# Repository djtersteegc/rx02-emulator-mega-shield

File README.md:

# rx02-emulator-mega-shield

Arduino Mega2560 shield with buttons and LCD based on [AK6DN's DEC RX02 emulator](https://github.com/AK6DN/rx02_emulator) board design and code.  There is a fork of his project at  https://github.com/djtersteegc/rx02_emulator that adds software support for the new board design.

You can also still run it via the original serial terminal command scheme.  If you don't want to build it with the LCD or buttons, you can disable supprort in the code by leaving

`#define USE_LCD_MENU`

commented out (undefined) in `my_project.h`

Resistor numbers is also different than AK6DN's original board so please refer to this mapping table below or the CSV file.

[Termination Resistor Table.csv](https://github.com/djtersteegc/rx02-emulator-mega-shield/blob/main/Termination%20Resistor%20Table.csv)

Most of the resistor footprints should NOT be populated.

| Signal         | Resistor | Value   | Resistor | Value   |
| -------------- | -------- | ------- | -------- | ------- |
| RX_DMA_MODE_H  | R2       | -       | R1       | **390** |
| RX_AC_L        | R4       | **120** | R3       | -       |
| RX_OUT_L       | R6       | -       | R5       | -       |
| RX_SHIFT_L     | R8       | -       | R7       | -       |
| RX_12BIT_L     | R10      | **180** | R9       | **390** |
| RX_DATA_L      | R12      | **180** | R11      | **390** |
| RX_DONE_L      | R14      | -       | R13      | -       |
| RX_XFER_RQST_L | R16      | -       | R15      | -       |
| RX_INIT_L      | R18      | -       | R17      | **390** |
| RX_ERROR_L     | R20      | -       | R19      | -       |
| RX_RUN_L       | R23      | **180** | R22      | **390** |

STL's and the [DesignSpark Mechanical](https://www.rs-online.com/designspark/mechanical-software) source file for an snap fit enclosure are in the **enclosure** directory. There is also a provision to secure it with one M3x6mm (or longer) screw if you want.  Since the power and USB port spacing on the Chinese clone Arduino Mega2560's with the CH340 serial chip is different than the original design there are two STL's for the case body, pick the one that matches your board.

All components can be sourced from the usual low cost China based vendors for a total build cost of around $20.  Please see the assembly page for more details.

[Hardware Component Choices and Assembly](https://djtersteegc.github.io/rx02-emulator-mega-shield/assembly.html)

An interactive BOM and parts placement diagram is also available.

[Interactive Bill of Materials (BOM)](https://djtersteegc.github.io/rx02-emulator-mega-shield/ibom.html)

# Getting a Board

You can download the Gerbers and use your favorite fab (JLCPCB, PCBWay, etc.) to make your own batch.  It's a standard two layer, 1oz copper board with dimensions of 99mm x 71mm so it squeaks under the 100mm x 100mm limit of the cheap Chinese fabs.

# Hardware Revisions

### Version 1.0

After designing and building the [Mega Pro SMD](https://github.com/djtersteegc/rx02-mega2560-pro) version of this, I discovered the reason you always had to do a ReINIT of the emulator to get it recognized was I failed to pick interrupt enabled pins on the Mega2560 for the RX_INIT and RX_RUN lines.  This has been corrected in the v1.1 board and you can fix this yourself in v1.0 by adding two jumper  wires from D22 to D2, and D26 to D3.  Once complete, reflash with the updated version of the code at https://github.com/djtersteegc/rx02_emulator 

### Version 1.1

Moved the RX_INIT and RX_RUN lines to interrupt enabled pins on the Mega2560.

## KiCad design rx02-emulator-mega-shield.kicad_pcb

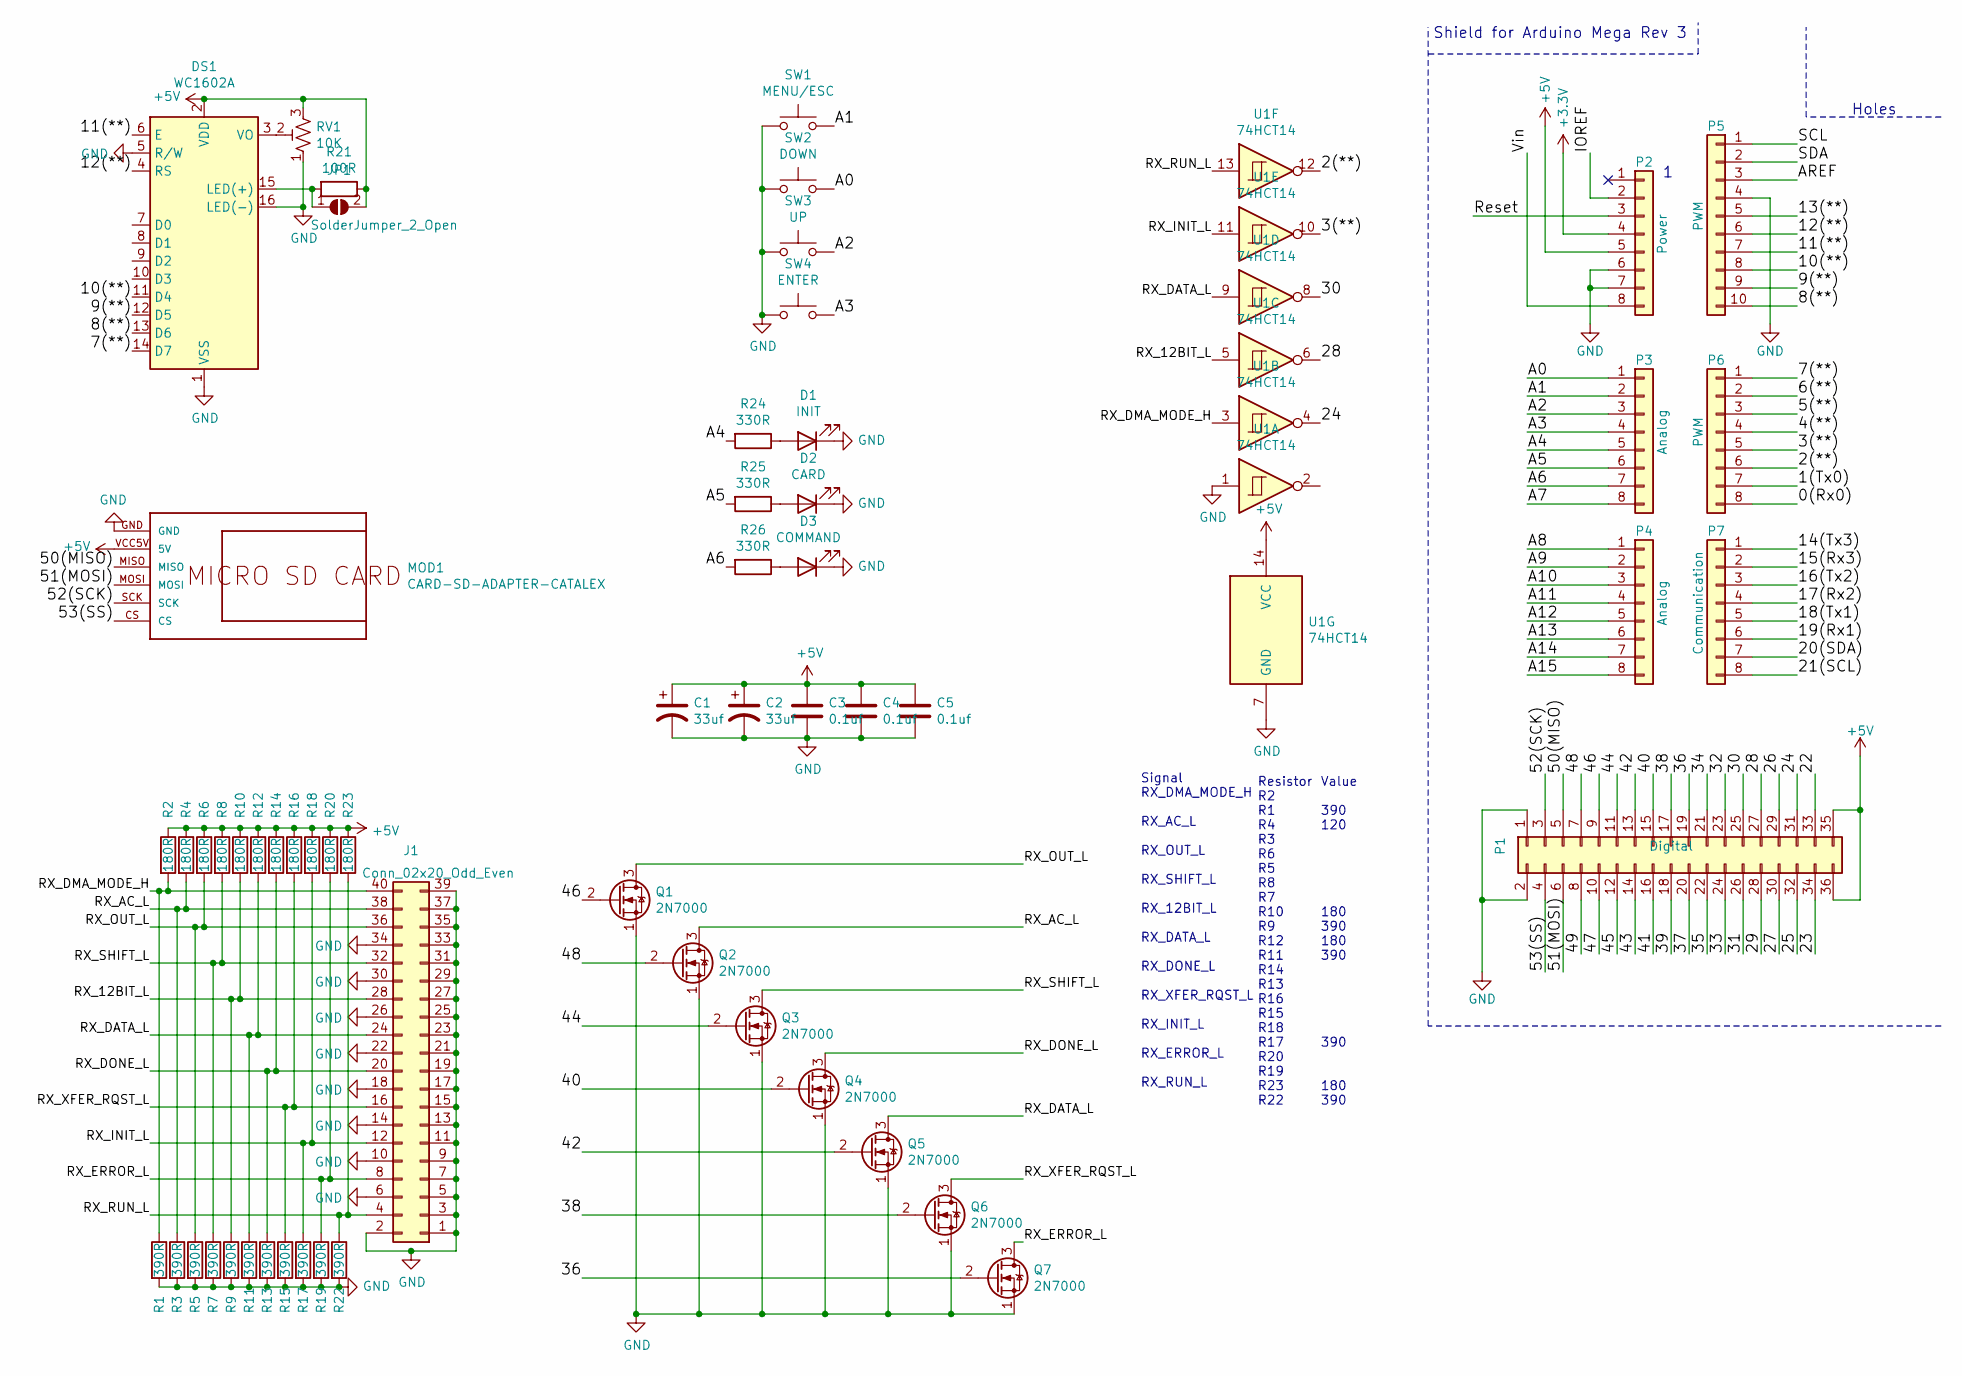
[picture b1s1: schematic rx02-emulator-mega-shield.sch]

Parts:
C1, C2: 33uf; CP_Radial_D5.0mm_P2.50mm
C3, C4, C5: 0.1uf; C_Disc_D5.0mm_W2.5mm_P5.00mm
D1: INIT; LED_D5.0mm
D2: CARD; LED_D5.0mm
D3: COMMAND; LED_D5.0mm
DS1: WC1602A
J1: Conn_02x20_Odd_Even; IDC-Header_2x20_P2.54mm_Vertical
JP1: SolderJumper_2_Open; SolderJumper-2_P1.3mm_Open_TrianglePad1.0x1.5mm
MOD1: CARD-SD-ADAPTER-CATALEX; Catalex-MicroSD-Card-Up
P1: Digital; Socket_Strip_Arduino_2x18
P2: Power; Socket_Strip_Arduino_1x08
P3, P4: Analog; Socket_Strip_Arduino_1x08
P5: PWM; Socket_Strip_Arduino_1x10
P6: PWM; Socket_Strip_Arduino_1x08
P7: Communication; Socket_Strip_Arduino_1x08
Q1, Q2, Q3, Q4, Q5, Q6, Q7: 2N7000; TO-92_HandSolder
R1, R3, R5, R7, R9, R11, R13, R15, R17, R19, R22: 390R; R_Axial_DIN0207_L6.3mm_D2.5mm_P7.62mm_Horizontal
R2, R4, R6, R8, R10, R12, R14, R16, R18, R20, R23: 180R; R_Axial_DIN0207_L6.3mm_D2.5mm_P7.62mm_Horizontal
R21: 100R; R_Axial_DIN0207_L6.3mm_D2.5mm_P7.62mm_Horizontal
R24, R25, R26: 330R; R_Axial_DIN0204_L3.6mm_D1.6mm_P5.08mm_Horizontal
RV1: 10K; TRIM_3362P-1-103
SW1: MENU/ESC; SW_PUSH_6mm_H4.3mm
SW2: DOWN; SW_PUSH_6mm_H4.3mm
SW3: UP; SW_PUSH_6mm_H4.3mm
SW4: ENTER; SW_PUSH_6mm_H4.3mm
U1: 74HCT14; DIP-14_W7.62mm_Socket_LongPads

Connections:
+3V3: P2.4
+5V: C1.1, C2.1, C3.1, C4.1, C5.1, DS1.2 (VDD), JP1.2 (B), MOD1.VCC5V (5V), P1.35, P1.36, P2.5, R2.1, R4.1, R6.1, R8.1, R10.1, R12.1, R14.1, R16.1, R18.1, R20.1, R21.1, R23.1, RV1.3, U1.14 (VCC)
/0(Rx0): P6.8
/1(Tx0): P6.7
/2(**): P6.6, U1.12
/3(**): P6.5, U1.10
/4(**): P6.4
/5(**): P6.3
/6(**): P6.2
/7(**): DS1.14 (D7), P6.1
/8(**): DS1.13 (D6), P5.10
/9(**): DS1.12 (D5), P5.9
/10(**): DS1.11 (D4), P5.8
/11(**): DS1.6 (E), P5.7
/12(**): DS1.4 (RS), P5.6
/13(**): P5.5
/14(Tx3): P7.1
/15(Rx3): P7.2
/16(Tx2): P7.3
/17(Rx2): P7.4
/18(Tx1): P7.5
/19(Rx1): P7.6
/20(SDA): P7.7
/21(SCL): P7.8
/22: P1.33
/23: P1.34
/24: P1.31, U1.4
/25: P1.32
/26: P1.29
/27: P1.30
/28: P1.27, U1.6
/29: P1.28
/30: P1.25, U1.8
/31: P1.26
/32: P1.23
/33: P1.24
/34: P1.21
/35: P1.22
/36: P1.19, Q7.2 (G)
/37: P1.20
/38: P1.17, Q6.2 (G)
/39: P1.18
/40: P1.15, Q4.2 (G)
/41: P1.16
/42: P1.13, Q5.2 (G)
/43: P1.14
/44: P1.11, Q3.2 (G)
/45: P1.12
/46: P1.9, Q1.2 (G)
/47: P1.10
/48: P1.7, Q2.2 (G)
/49: P1.8
/50(MISO): MOD1.MISO, P1.5
/51(MOSI): MOD1.MOSI, P1.6
/52(SCK): MOD1.SCK, P1.3
/53(SS): MOD1.CS, P1.4
/A0: P3.1, SW2.2
/A1: P3.2, SW1.2
/A2: P3.3, SW3.2
/A3: P3.4, SW4.2
/A4: P3.5, R24.2
/A5: P3.6, R25.2
/A6: P3.7, R26.2
/A7: P3.8
/A8: P4.1
/A9: P4.2
/A10: P4.3
/A11: P4.4
/A12: P4.5
/A13: P4.6
/A14: P4.7
/A15: P4.8
/AREF: P5.3
/IOREF: P2.2
/RX_12BIT_L: J1.28, R9.1, R10.2, U1.5
/RX_AC_L: J1.38, Q2.3 (D), R3.1, R4.2
/RX_DATA_L: J1.24, Q5.3 (D), R11.1, R12.2, U1.9
/RX_DMA_MODE_H: J1.40, R1.1, R2.2, U1.3
/RX_DONE_L: J1.20, Q4.3 (D), R13.1, R14.2
/RX_ERROR_L: J1.8, Q7.3 (D), R19.1, R20.2
/RX_INIT_L: J1.12, R17.1, R18.2, U1.11
/RX_OUT_L: J1.36, Q1.3 (D), R5.1, R6.2
/RX_RUN_L: J1.4, R22.1, R23.2, U1.13
/RX_SHIFT_L: J1.32, Q3.3 (D), R7.1, R8.2
/RX_XFER_RQST_L: J1.16, Q6.3 (D), R15.1, R16.2
/Reset: P2.3
/SCL: P5.1
/SDA: P5.2
/Vin: P2.8
GND: C1.2, C2.2, C3.2, C4.2, C5.2, D1.1 (K), D2.1 (K), D3.1 (K), DS1.1 (VSS), DS1.5 (R/W), DS1.16 (LED(-)), J1.1, J1.2, J1.3, J1.5, J1.6, J1.7, J1.9, J1.10, J1.11, J1.13, J1.14, J1.15, J1.17, J1.18, J1.19, J1.21, J1.22, J1.23, J1.25, J1.26, J1.27, J1.29, J1.30, J1.31, J1.33, J1.34, J1.35, J1.37, J1.39, MOD1.GND, P1.1, P1.2, P2.6, P2.7, P5.4, Q1.1 (S), Q2.1 (S), Q3.1 (S), Q4.1 (S), Q5.1 (S), Q6.1 (S), Q7.1 (S), R1.2, R3.2, R5.2, R7.2, R9.2, R11.2, R13.2, R15.2, R17.2, R19.2, R22.2, RV1.1, SW1.1, SW2.1, SW3.1, SW4.1, U1.1, U1.7 (GND)
unnamed: D1.2 (A), R24.1
unnamed: D2.2 (A), R25.1
unnamed: D3.2 (A), R26.1
unnamed: DS1.3 (VO), RV1.2
unnamed: DS1.15 (LED(+)), JP1.1 (A), R21.2

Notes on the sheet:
Shield for Arduino Mega Rev 3
Holes
Signal RX_DMA_MODE_H RX_AC_L RX_OUT_L RX_SHIFT_L RX_12BIT_L RX_DATA_L RX_DONE_L RX_XFER_RQST_L RX_INIT_L RX_ERROR_L RX_RUN_L
Resistor R2 R1 R4 R3 R6 R5 R8 R7 R10 R9 R12 R11 R14 R13 R16 R15 R18 R17 R20 R19 R23 R22
Value 390 120 180 390 180 390 390 180 390

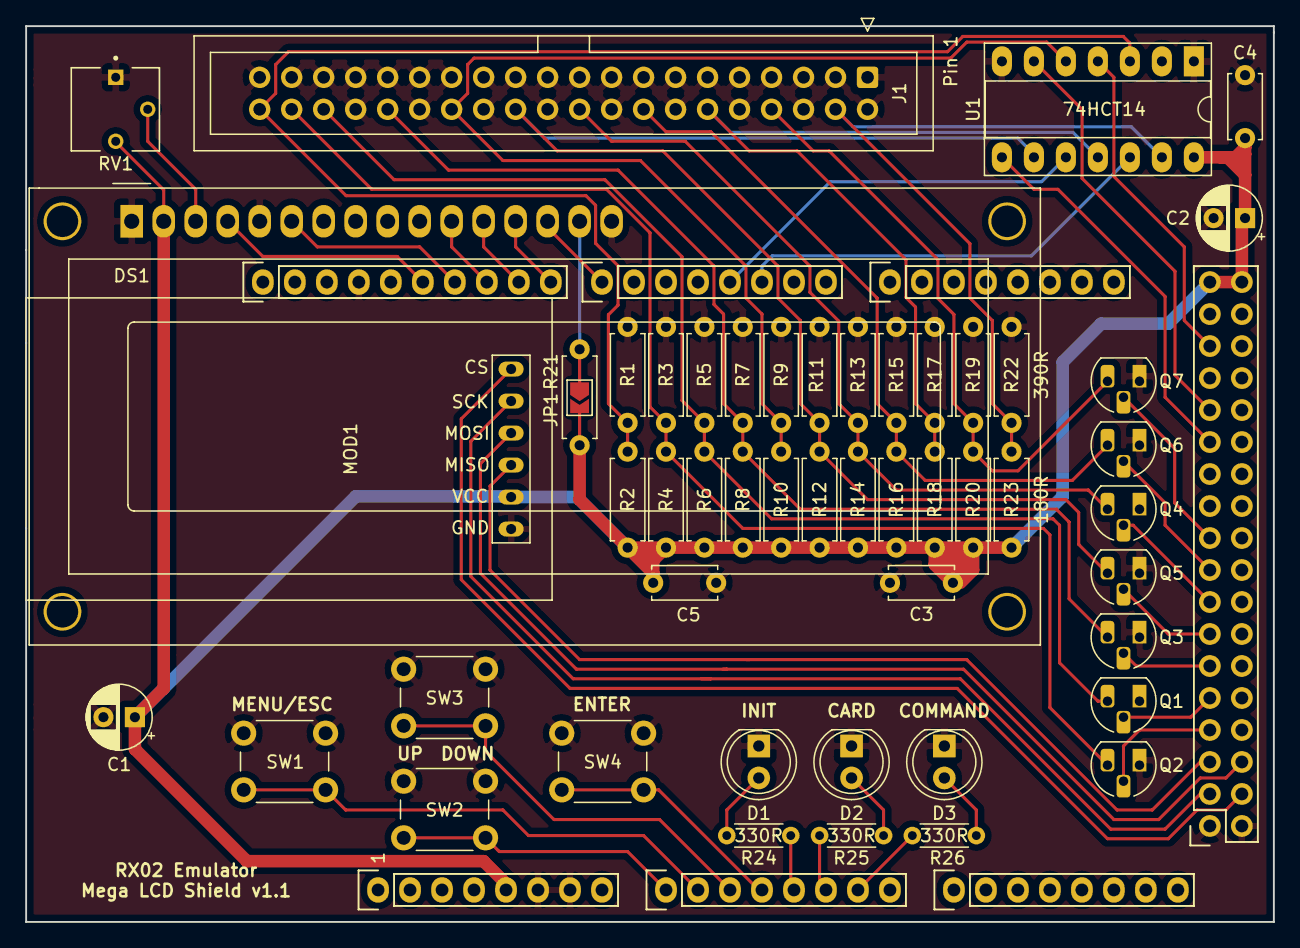
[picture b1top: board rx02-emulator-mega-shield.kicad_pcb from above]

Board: 2 copper layers, 99.1 x 71.1 mm, 58 parts (0 on the bottom side), 47 nets.

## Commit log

2022-09-05 Board version 1.0
2022-09-05 Fix pictures
2022-09-05 Copy fixes
2022-09-26 Add resistor termination table for the new board since the numbers is not the same as Don's original board
2022-10-08 Fix 3D models
2022-10-08 Add enlosure
2022-10-08 Update README with enclosure and resistor table instructions
2023-10-12 Update to v1.1 board
2023-11-26 Add resistor table to README
